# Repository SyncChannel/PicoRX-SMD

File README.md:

# PicoRX-SMD

A compact implementation of the PicoRX circuit design using SMD components. KiCad files are included. Four layer PCB.

See information about the original project here:

https://github.com/dawsonjon/PicoRX

https://101-things.readthedocs.io/en/latest/breadboard_radio.html

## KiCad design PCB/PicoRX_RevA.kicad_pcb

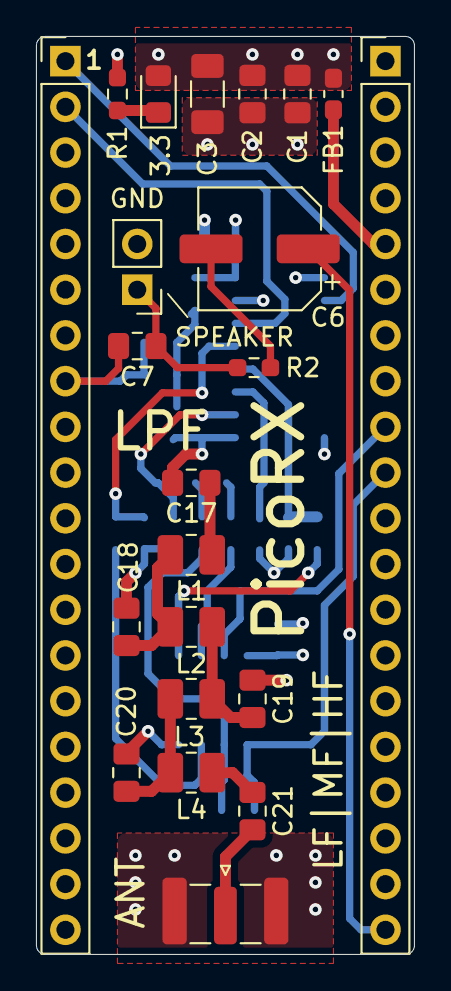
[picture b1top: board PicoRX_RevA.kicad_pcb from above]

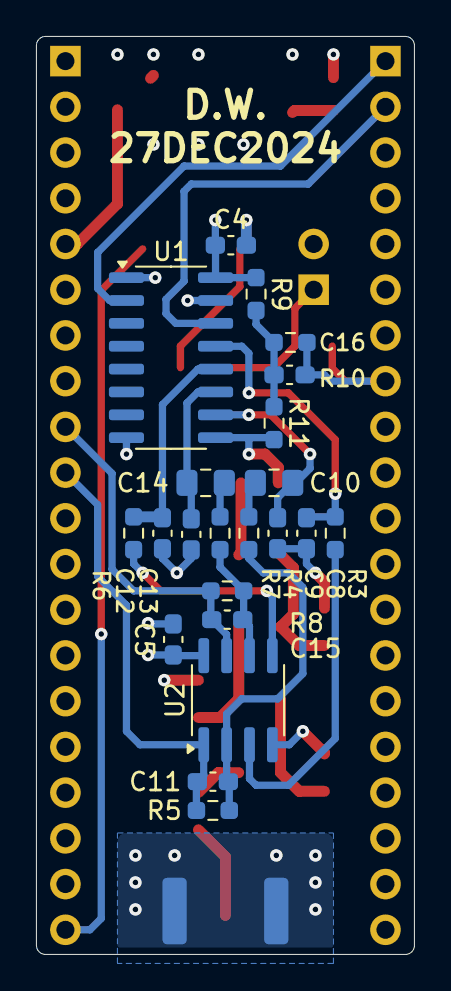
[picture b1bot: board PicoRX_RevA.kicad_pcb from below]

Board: 4 copper layers, 21.0 x 51.0 mm, 44 parts (22 on the bottom side), 29 nets.

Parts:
C1, C17, C21: 10n; C_0805_2012Metric_Pad1.18x1.45mm_HandSolder
C2: 1u; C_0805_2012Metric_Pad1.18x1.45mm_HandSolder
C3: 10u; C_1206_3216Metric_Pad1.33x1.80mm_HandSolder
C4, C5, C16: 100n; C_0603_1608Metric_Pad1.08x0.95mm_HandSolder
C6: 100u; CP_Elec_6.3x7.7
C7: 470n; C_0805_2012Metric_Pad1.18x1.45mm_HandSolder
C8, C9, C12, C13: 56n; C_0603_1608Metric_Pad1.08x0.95mm_HandSolder
C10, C14: 10u; C_0805_2012Metric_Pad1.18x1.45mm_HandSolder
C11, C15: 220p; C_0603_1608Metric_Pad1.08x0.95mm_HandSolder
C18, C19: 150p; C_0805_2012Metric_Pad1.18x1.45mm_HandSolder
C20: 130p; C_0805_2012Metric_Pad1.18x1.45mm_HandSolder
D1: LED; LED_0805_2012Metric_Pad1.15x1.40mm_HandSolder
FB1: FerriteBead; L_0603_1608Metric_Pad1.05x0.95mm_HandSolder
J1, J2: Conn_01x20_Pin; PinHeader_1x20_P2.54mm_Vertical
J3: Conn_01x02_Pin; PinHeader_1x02_P2.54mm_Vertical
J4: Conn_Coaxial; SMA_Samtec_SMA-J-P-H-ST-EM1_EdgeMount
L1: 560n; L_1008_2520Metric_Pad1.43x2.20mm_HandSolder
L2, L3: 680n; L_1008_2520Metric_Pad1.43x2.20mm_HandSolder
L4: 470n; L_1008_2520Metric_Pad1.43x2.20mm_HandSolder
R1: 470; R_0603_1608Metric_Pad0.98x0.95mm_HandSolder
R2: 100; R_0603_1608Metric_Pad0.98x0.95mm_HandSolder
R3, R4, R6, R7: 82; R_0603_1608Metric_Pad0.98x0.95mm_HandSolder
R5, R8: 56k; R_0603_1608Metric_Pad0.98x0.95mm_HandSolder
R9: 10k; R_0603_1608Metric_Pad0.98x0.95mm_HandSolder
R10: 10K; R_0603_1608Metric_Pad0.98x0.95mm_HandSolder
R11: 1k; R_0603_1608Metric_Pad0.98x0.95mm_HandSolder
U1: SN74CBTLV3253; SOIC-16_3.9x9.9mm_P1.27mm
U2: MCP6022; SOIC-8_3.9x4.9mm_P1.27mm

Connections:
+3.3VA: C1.1, C2.1, C3.1, C4.1, C5.1, D1.2 (A), FB1.1, R9.2, U1.16 (VCC), U2.8 (V+)
/LO_I: J1.2, U1.14 (S0)
/LO_Q: J1.1, U1.2 (S1)
/RX_I: C15.2, J2.9, R8.2, U2.7
/RX_Q: C11.2, J2.10, R5.2, U2.1
/SPEAKER: C6.1, J2.20
GND: C1.2, C2.2, C3.2, C4.2, C5.2, C7.1, C8.2, C9.2, C12.2, C13.2, C16.2, C18.2, C19.2, C20.2, J1.3, J1.8, J1.13, J1.18, J2.3, J2.13, J2.18, J3.2, J4.2 (Ext), R1.1, R10.1, U1.1 (1~OE), U1.8 (GND), U1.15 (2~OE), U2.4 (V-)
unnamed: C6.2, R2.1
unnamed: C10.2, R4.1
unnamed: C14.2, R7.1
unnamed: C16.1, R9.1, R10.2, R11.2
unnamed: C17.1, L1.2
unnamed: C18.1, L1.1, L2.2
unnamed: C19.1, L2.1, L3.2
unnamed: C20.1, L3.1, L4.2
unnamed: C21.2, L4.1
unnamed: D1.1 (K), R1.2
unnamed: FB1.2, J2.5
unnamed: C7.2, J3.1, R2.2
unnamed: C21.1, J4.1 (In)
unnamed: C17.2, R11.1, U1.9 (2A)
unnamed: C9.1, C10.1, U1.10 (2B1)
unnamed: C13.1, C14.1, U1.11 (2B2)
unnamed: C12.1, R6.1, U1.12 (2B3)
unnamed: C8.1, R3.1, U1.13 (2B4)
unnamed: R3.2, U2.3 (+)
unnamed: C11.1, R4.2, R5.1, U2.2 (-)
unnamed: R6.2, U2.5 (+)
unnamed: C15.1, R7.2, R8.1, U2.6 (-)

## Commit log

2025-03-12 Added PCB files
